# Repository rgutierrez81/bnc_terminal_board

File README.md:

#Labjack T7 code, boards and schematics used in cold atoms experiments. 

CODE:

-Functions and libraries:

functionscontrol.py

-Contro system:
stream_out_FIO.py

PCB HARDWARE:

-Eagle Schematic and Board files in:

180216RGDS_esquematico_Y7.brd
180216RGDS_esquematico_Y7.sch

-Gerber files on zip file:

180216RGDS_esquematico_Y7.zip

-DXF panel file in:

180216RGDS_esquematico_Y7_Panel.dxf

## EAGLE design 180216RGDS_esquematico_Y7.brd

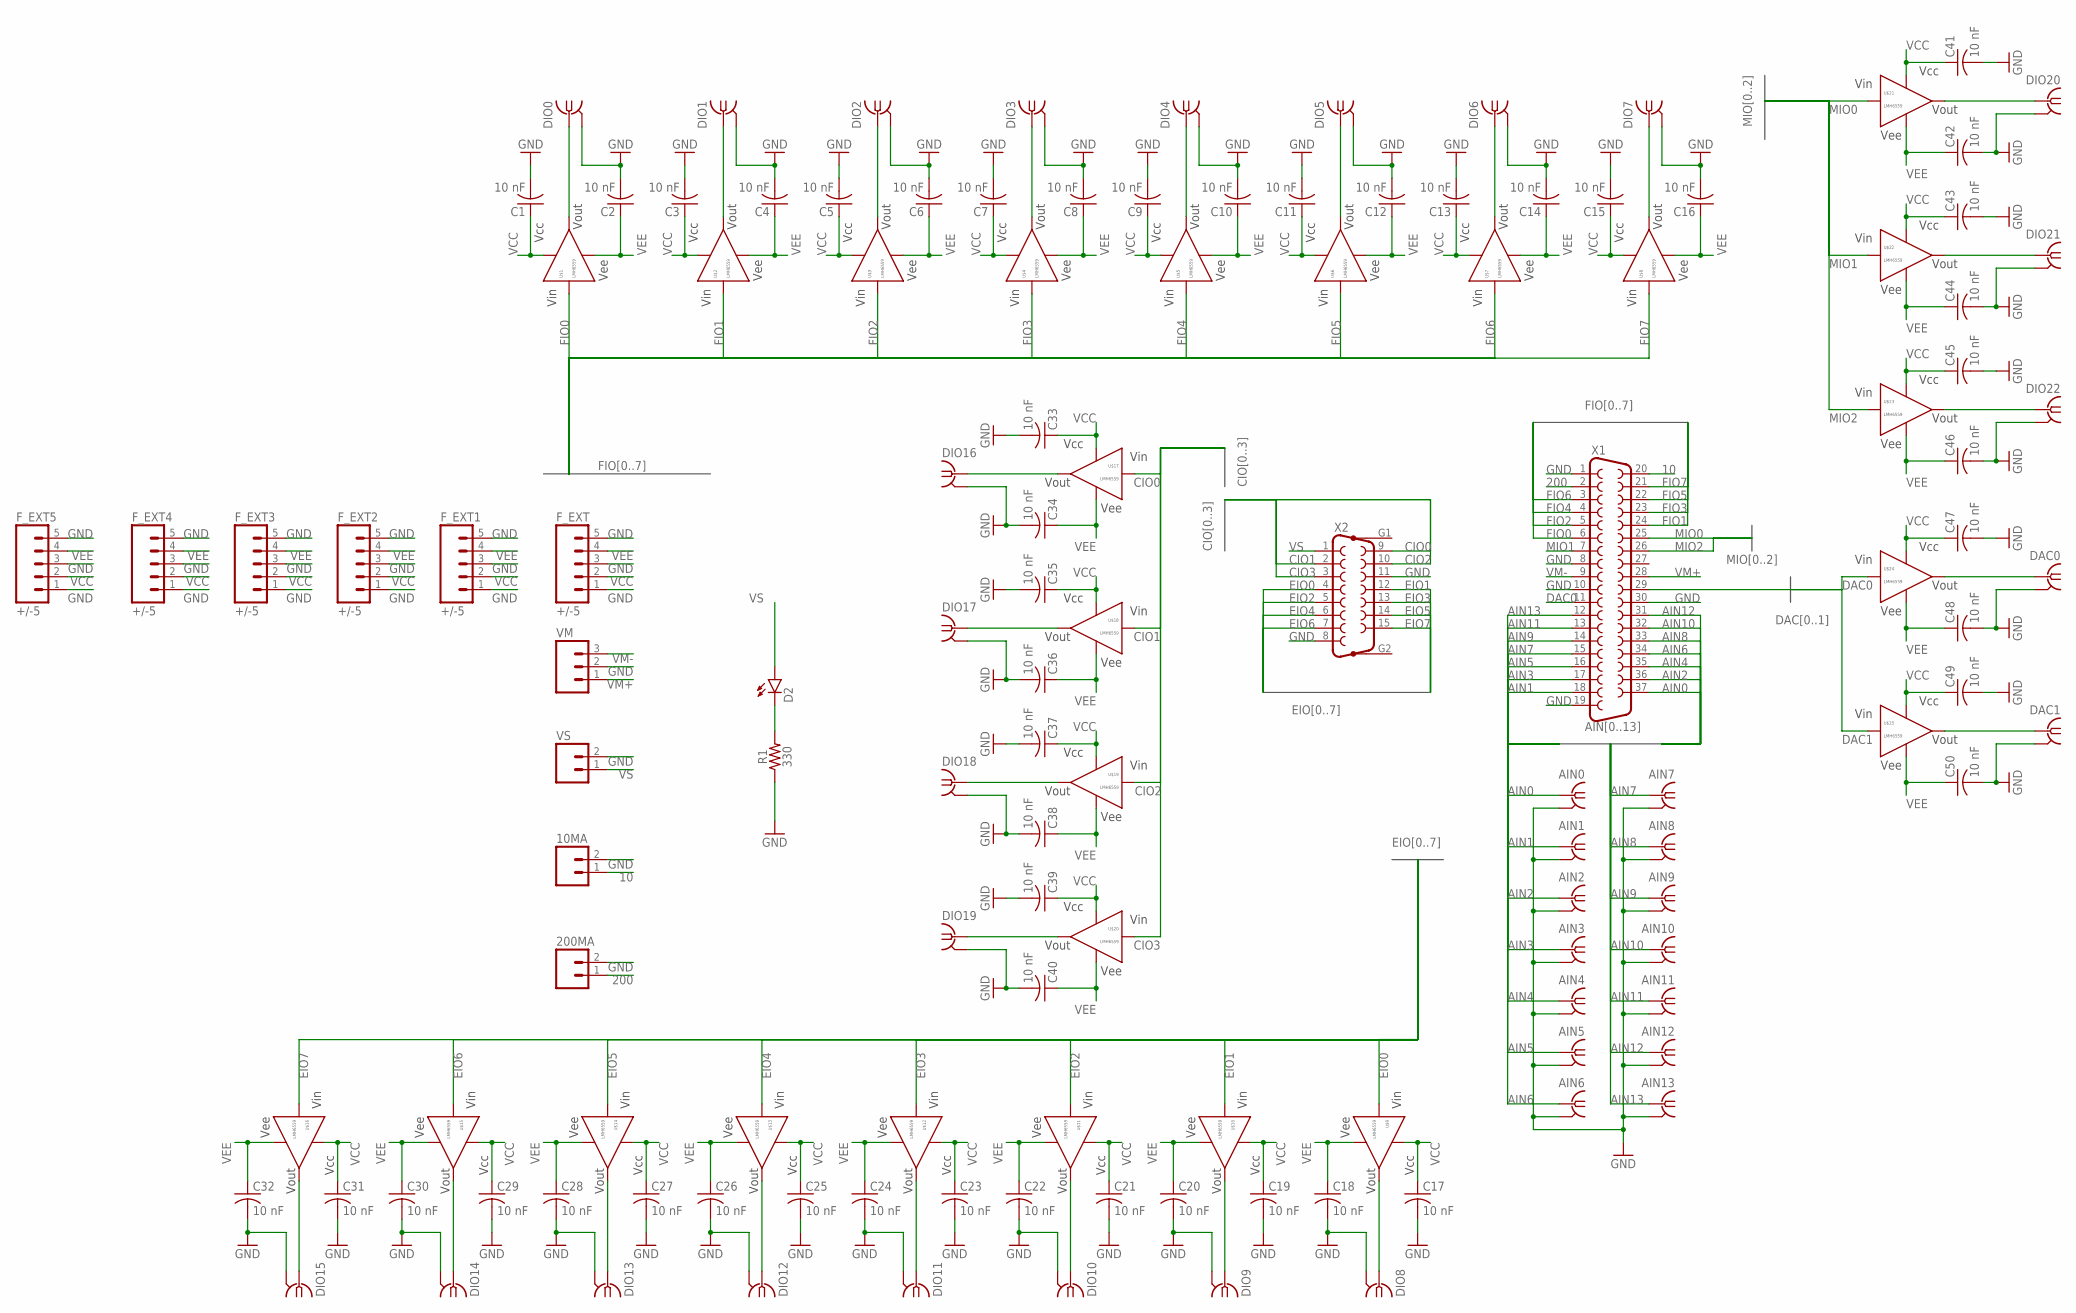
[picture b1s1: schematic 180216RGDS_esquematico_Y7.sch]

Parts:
10MA, 200MA: M02PTH; 1X02
AIN0, AIN1, AIN2, AIN3, AIN4, AIN5, AIN6, AIN7, AIN8, AIN9, AIN10, AIN11, AIN12, AIN13: TE5227222-1; VERTICAL_PCB&PANEL_TE
C1, C2, C3, C4, C5, C6, C7, C8, C9, C10, C11, C12, C13, C14, C15, C16, C17, C18, C19, C20, C21, C22, C23, C24, C25, C26, C27, C28, C29, C30, C31, C32, C33, C34, C35, C36, C37, C38, C39, C40, C41, C42, C43, C44, C45, C46, C47, C48, C49, C50: 10 nF; C1206K
D2: LED5MM
DAC0, DAC1: TE5227222-1; VERTICAL_PCB&PANEL_TE
DIO0, DIO1, DIO2, DIO3, DIO4, DIO5, DIO6, DIO7, DIO8, DIO9, DIO10, DIO11, DIO12, DIO13, DIO14, DIO15, DIO16, DIO17, DIO18, DIO19, DIO20, DIO21, DIO22: TE5227222-1; VERTICAL_PCB&PANEL_TE
F_EXT, F_EXT1, F_EXT2, F_EXT3, F_EXT4, F_EXT5: +/-5; 1X05
R1: 330; AXIAL-0.3
U$1, U$2, U$3, U$4, U$5, U$6, U$7, U$8, U$9, U$10, U$11, U$12, U$13, U$14, U$15, U$16, U$17, U$18, U$19, U$20, U$21, U$22, U$23, U$24, U$25: LMH6559; SO08
VM: M03PTH; 1X03
VS: M02PTH; 1X02
X1: F37HP
X2: F15HP

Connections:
10: 10MA.1, X1.20
200: 200MA.1, X1.2
AIN0: AIN0.S (1), X1.37
AIN1: AIN1.S (1), X1.18
AIN2: AIN2.S (1), X1.36
AIN3: AIN3.S (1), X1.17
AIN4: AIN4.S (1), X1.35
AIN5: AIN5.S (1), X1.16
AIN6: AIN6.S (1), X1.34
AIN7: AIN7.S (1), X1.15
AIN8: AIN8.S (1), X1.33
AIN9: AIN9.S (1), X1.14
AIN10: AIN10.S (1), X1.32
AIN11: AIN11.S (1), X1.13
AIN12: AIN12.S (1), X1.31
AIN13: AIN13.S (1), X1.12
CIO0: U$17.4 (VIN), X2.9
CIO1: U$18.4 (VIN), X2.2
CIO2: U$19.4 (VIN), X2.10
CIO3: U$20.4 (VIN), X2.3
DAC0: U$24.4 (VIN), X1.11
DAC1: U$25.4 (VIN), X1.29
EIO0: U$9.4 (VIN), X2.4
EIO1: U$10.4 (VIN), X2.12
EIO2: U$11.4 (VIN), X2.5
EIO3: U$12.4 (VIN), X2.13
EIO4: U$13.4 (VIN), X2.6
EIO5: U$14.4 (VIN), X2.14
EIO6: U$15.4 (VIN), X2.7
EIO7: U$16.4 (VIN), X2.15
FIO0: U$1.4 (VIN), X1.6
FIO1: U$2.4 (VIN), X1.24
FIO2: U$3.4 (VIN), X1.5
FIO3: U$4.4 (VIN), X1.23
FIO4: U$5.4 (VIN), X1.4
FIO5: U$6.4 (VIN), X1.22
FIO6: U$7.4 (VIN), X1.3
FIO7: U$8.4 (VIN), X1.21
GND: 10MA.2, 200MA.2, AIN0.G (2), AIN1.G (2), AIN2.G (2), AIN3.G (2), AIN4.G (2), AIN5.G (2), AIN6.G (2), AIN7.G (2), AIN8.G (2), AIN9.G (2), AIN10.G (2), AIN11.G (2), AIN12.G (2), AIN13.G (2), C1.2, C2.2, C3.2, C4.2, C5.2, C6.2, C7.2, C8.2, C9.2, C10.2, C11.2, C12.2, C13.2, C14.2, C15.2, C16.2, C17.2, C18.2, C19.2, C20.2, C21.2, C22.2, C23.2, C24.2, C25.2, C26.2, C27.2, C28.2, C29.2, C30.2, C31.2, C32.2, C33.2, C34.2, C35.2, C36.2, C37.2, C38.2, C39.2, C40.2, C41.2, C42.2, C43.2, C44.2, C45.2, C46.2, C47.2, C48.2, C49.2, C50.2, DAC0.G (2), DAC1.G (2), DIO0.G (2), DIO1.G (2), DIO2.G (2), DIO3.G (2), DIO4.G (2), DIO5.G (2), DIO6.G (2), DIO7.G (2), DIO8.G (2), DIO9.G (2), DIO10.G (2), DIO11.G (2), DIO12.G (2), DIO13.G (2), DIO14.G (2), DIO15.G (2), DIO16.G (2), DIO17.G (2), DIO18.G (2), DIO19.G (2), DIO20.G (2), DIO21.G (2), DIO22.G (2), F_EXT.1, F_EXT.3, F_EXT.5, F_EXT1.1, F_EXT1.3, F_EXT1.5, F_EXT2.1, F_EXT2.3, F_EXT2.5, F_EXT3.1, F_EXT3.3, F_EXT3.5, F_EXT4.1, F_EXT4.3, F_EXT4.5, F_EXT5.1, F_EXT5.3, F_EXT5.5, R1.P$1 (1), VM.2, VS.2, X1.1, X1.8, X1.10, X1.19, X1.30, X2.8, X2.11
MIO0: U$21.4 (VIN), X1.25
MIO1: U$22.4 (VIN), X1.7
MIO2: U$23.4 (VIN), X1.26
unnamed: DIO0.S (1), U$1.8 (VOUT)
unnamed: D2.K (C), R1.P$2 (2)
unnamed: DIO1.S (1), U$2.8 (VOUT)
unnamed: DIO2.S (1), U$3.8 (VOUT)
unnamed: DIO3.S (1), U$4.8 (VOUT)
unnamed: DIO4.S (1), U$5.8 (VOUT)
unnamed: DIO5.S (1), U$6.8 (VOUT)
unnamed: DIO6.S (1), U$7.8 (VOUT)
unnamed: DIO7.S (1), U$8.8 (VOUT)
unnamed: DIO8.S (1), U$9.8 (VOUT)
unnamed: DIO9.S (1), U$10.8 (VOUT)
unnamed: DIO10.S (1), U$11.8 (VOUT)
unnamed: DIO11.S (1), U$12.8 (VOUT)
unnamed: DIO12.S (1), U$13.8 (VOUT)
unnamed: DIO13.S (1), U$14.8 (VOUT)
unnamed: DIO14.S (1), U$15.8 (VOUT)
unnamed: DIO15.S (1), U$16.8 (VOUT)
unnamed: DIO16.S (1), U$17.8 (VOUT)
unnamed: DIO17.S (1), U$18.8 (VOUT)
unnamed: DIO18.S (1), U$19.8 (VOUT)
unnamed: DIO19.S (1), U$20.8 (VOUT)
unnamed: DIO20.S (1), U$21.8 (VOUT)
unnamed: DIO21.S (1), U$22.8 (VOUT)
unnamed: DIO22.S (1), U$23.8 (VOUT)
unnamed: DAC0.S (1), U$24.8 (VOUT)
unnamed: DAC1.S (1), U$25.8 (VOUT)
VCC: C1.1, C3.1, C5.1, C7.1, C9.1, C11.1, C13.1, C15.1, C17.1, C19.1, C21.1, C23.1, C25.1, C27.1, C29.1, C31.1, C33.1, C35.1, C37.1, C39.1, C41.1, C43.1, C45.1, C47.1, C49.1, F_EXT.2, F_EXT1.2, F_EXT2.2, F_EXT3.2, F_EXT4.2, F_EXT5.2, U$1.1 (VCC), U$2.1 (VCC), U$3.1 (VCC), U$4.1 (VCC), U$5.1 (VCC), U$6.1 (VCC), U$7.1 (VCC), U$8.1 (VCC), U$9.1 (VCC), U$10.1 (VCC), U$11.1 (VCC), U$12.1 (VCC), U$13.1 (VCC), U$14.1 (VCC), U$15.1 (VCC), U$16.1 (VCC), U$17.1 (VCC), U$18.1 (VCC), U$19.1 (VCC), U$20.1 (VCC), U$21.1 (VCC), U$22.1 (VCC), U$23.1 (VCC), U$24.1 (VCC), U$25.1 (VCC)
VEE: C2.1, C4.1, C6.1, C8.1, C10.1, C12.1, C14.1, C16.1, C18.1, C20.1, C22.1, C24.1, C26.1, C28.1, C30.1, C32.1, C34.1, C36.1, C38.1, C40.1, C42.1, C44.1, C46.1, C48.1, C50.1, F_EXT.4, F_EXT1.4, F_EXT2.4, F_EXT3.4, F_EXT4.4, F_EXT5.4, U$1.5 (VEE), U$2.5 (VEE), U$3.5 (VEE), U$4.5 (VEE), U$5.5 (VEE), U$6.5 (VEE), U$7.5 (VEE), U$8.5 (VEE), U$9.5 (VEE), U$10.5 (VEE), U$11.5 (VEE), U$12.5 (VEE), U$13.5 (VEE), U$14.5 (VEE), U$15.5 (VEE), U$16.5 (VEE), U$17.5 (VEE), U$18.5 (VEE), U$19.5 (VEE), U$20.5 (VEE), U$21.5 (VEE), U$22.5 (VEE), U$23.5 (VEE), U$24.5 (VEE), U$25.5 (VEE)
VM+: VM.1, X1.28
VM-: VM.3, X1.9
VS: D2.A, VS.1, X2.1

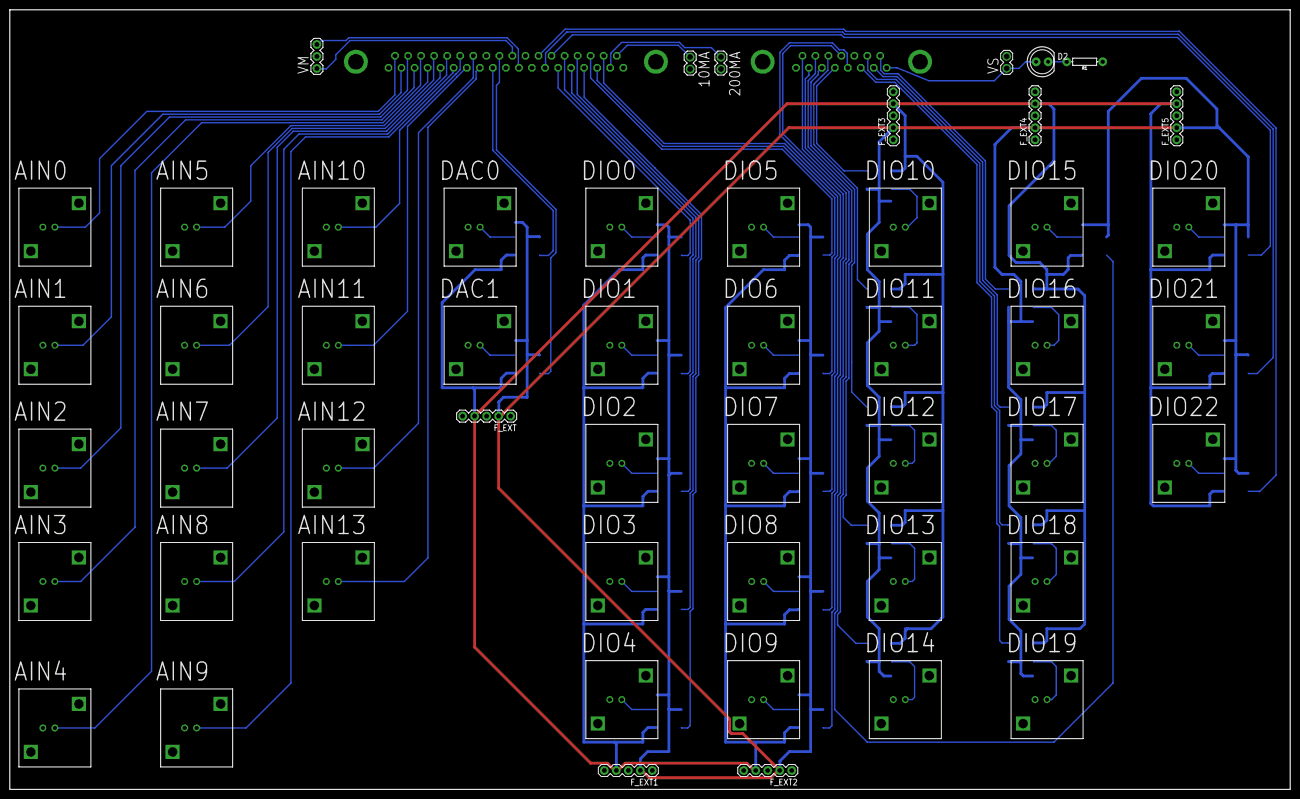
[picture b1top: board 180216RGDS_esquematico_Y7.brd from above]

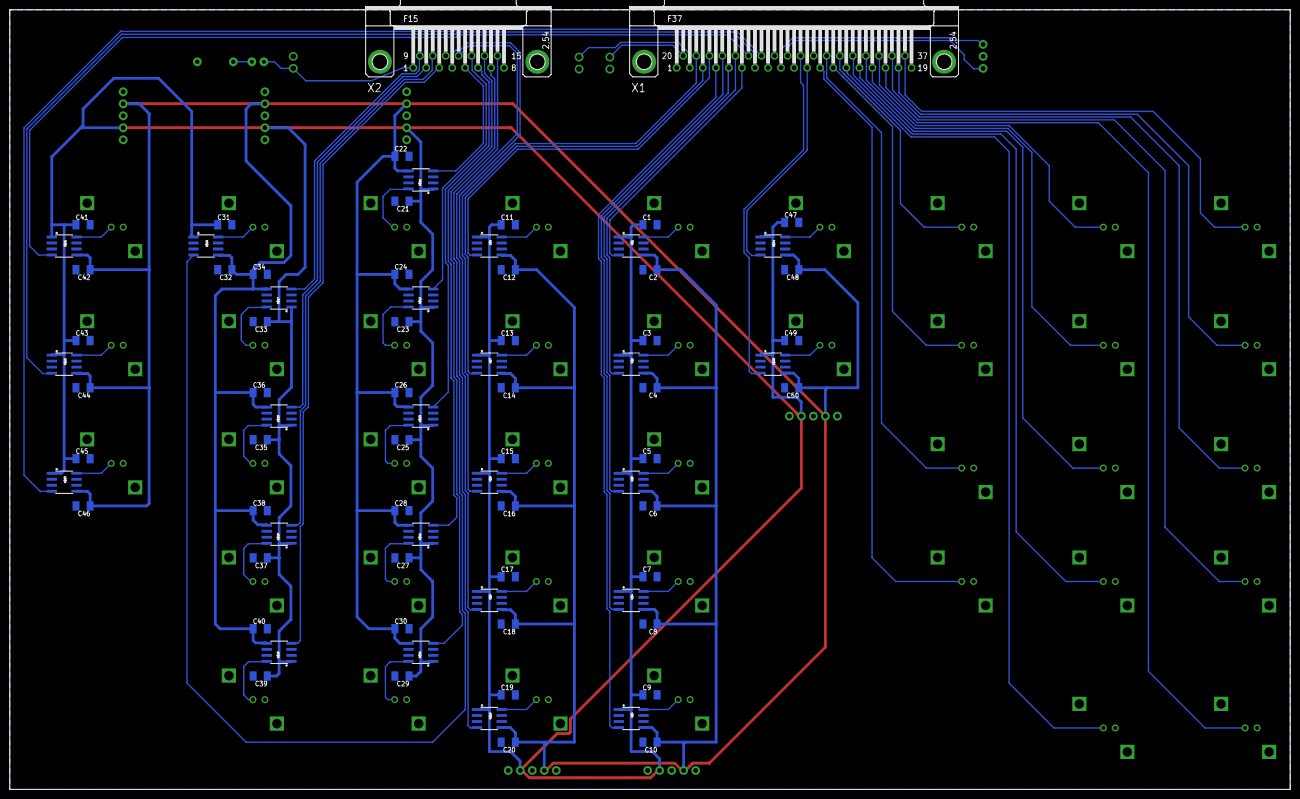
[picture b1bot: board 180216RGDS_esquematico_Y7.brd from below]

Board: 2 copper layers, 271.0 x 165.0 mm, 128 parts (77 on the bottom side), 73 nets.

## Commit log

2021-07-02 Create LICENSE

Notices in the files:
parts and their libraries:
SparkFun-Connectors: Licensing: Creative Commons ShareAlike 4.0 International - https://creativecommons.org/licenses/by-sa/4.0
